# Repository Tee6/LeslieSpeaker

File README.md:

# LeslieSpeaker
Im Rahmen des HWE Projekts wurde ein Leslie Lautsprecher realisiert. Teammitglieder: Pius Bickel, Niko Leimegger

Dokumentation unter: "Dokumentation und Projektanfrage/Leslie_Speaker_Doku_Bickel_Leimegger.pdf"

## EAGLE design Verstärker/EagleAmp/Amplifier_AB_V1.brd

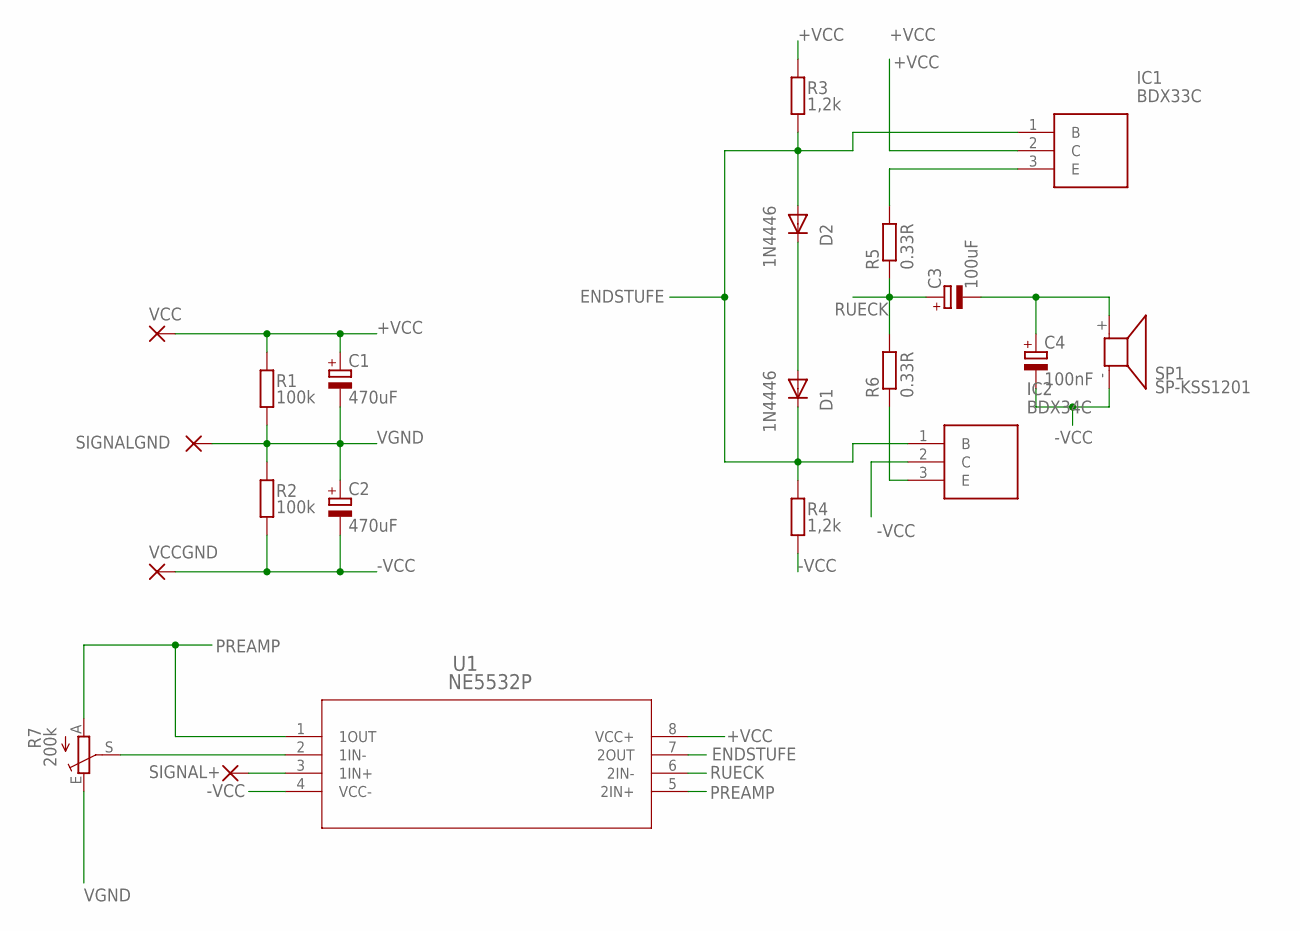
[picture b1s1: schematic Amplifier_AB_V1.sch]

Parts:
C1, C2: 470uF; 2,5-5
C3: 100uF; 5-10,5
C4: 100nF; 5-10,5
D1, D2: 1N4446; DO35-10
IC1: BDX33C; TO270P460X1020X2008-3P
IC2: BDX34C; TO270P460X1020X2008-3P
R1, R2: 100k; 0207/10
R3, R4: 1,2k; 0207/10
R5, R6: 0.33R; 0309/12
R7: 200k; CT6
SIGNAL+: 2,15/1,0
SIGNALGND: 2,15/1,0
SP1: SP-KSS1201
U1: NE5532P; P8
VCC: 2,15/1,0
VCCGND: 2,15/1,0

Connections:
+VCC: C1.+, IC1.2 (C), R1.2, R3.2, U1.8 (VCC+), VCC.1
-VCC: C2.-, C4.-, IC2.2 (C), R2.1, R4.1, SP1.- (2), U1.4 (VCC-), VCCGND.1
ENDSTUFE: D1.C, D2.A, IC1.1 (B), IC2.1 (B), R3.1, R4.2, U1.7 (2OUT)
unnamed: IC1.3 (E), R5.2
unnamed: R7.S, U1.2 (1IN-)
unnamed: C3.-, C4.+, SP1.+ (1)
unnamed: D1.A, D2.C
unnamed: IC2.3 (E), R6.1
unnamed: SIGNAL+.1, U1.3 (1IN+)
PREAMP: R7.A, U1.1 (1OUT), U1.5 (2IN+)
RUECK: C3.+, R5.1, R6.2, U1.6 (2IN-)
VGND: C1.-, C2.+, R1.1, R2.2, R7.E, SIGNALGND.1

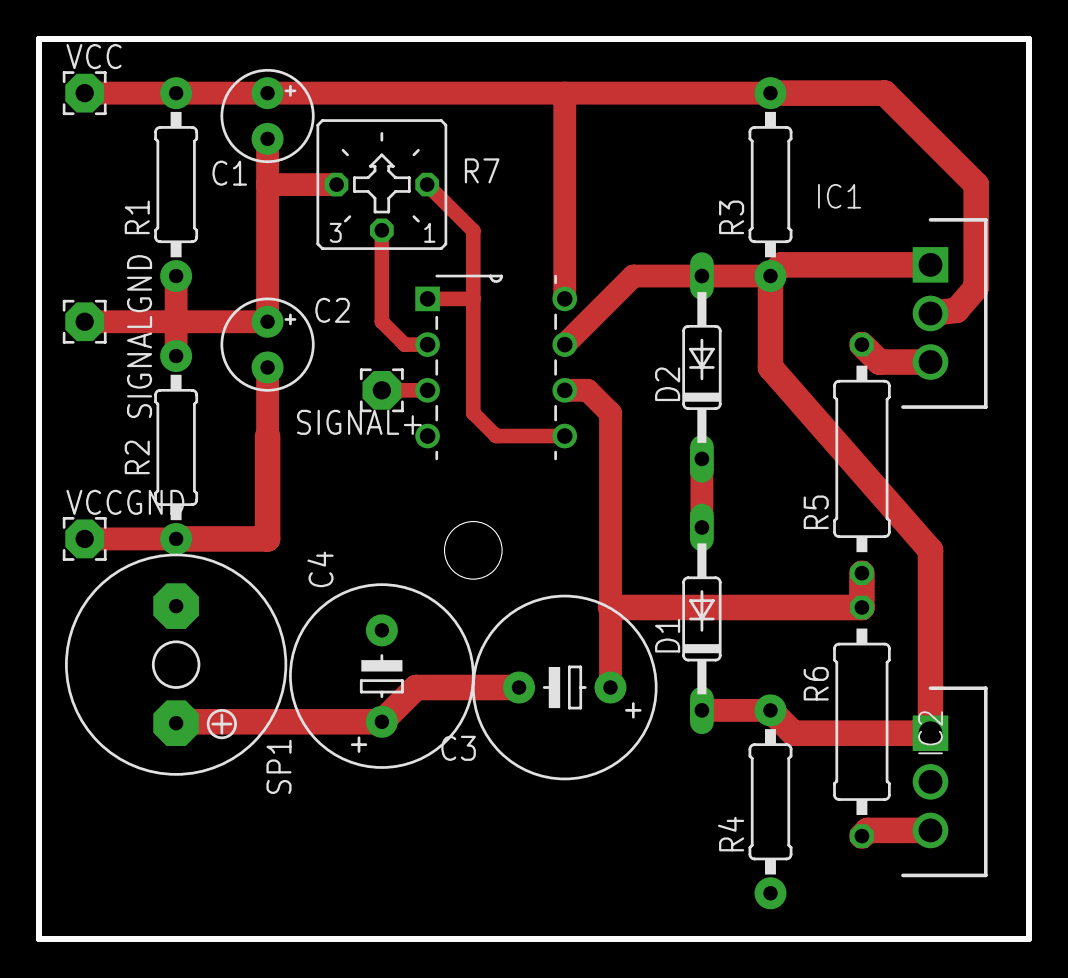
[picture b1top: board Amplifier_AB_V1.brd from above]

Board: 2 copper layers, 55.0 x 50.0 mm, 21 parts (0 on the bottom side), 12 nets.

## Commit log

2023-06-22 Fertige Ábgabe

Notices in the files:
parts and their libraries:
COPYRIGHT: Copyright (C) 2023 Ultra Librarian. All rights reserved.
